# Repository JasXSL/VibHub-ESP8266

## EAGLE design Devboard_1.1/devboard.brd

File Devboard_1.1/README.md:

# Work in progress

Goal is to correct the errors in rev 1.0 and make additional improvements in the case additional devboard PCBs are made (likely given how cheap that is)

## TODO

~~Swap SDA/SCL pins on ESP8266 and header~~

~~Change I2C address to something not reserved (https://www.i2c-bus.org/addressing/)~~
Uses 0x60

~~Replace resistor array package to fit 0402 that the EXB28V actually uses (never trust what summary descriptions show)~~ Using EXB38V/0603x4 instead

~~Move buttons, obstructed by plugin boards~~

~~Add LED to driver enable/sleep, GPIO15~~

~~Add 0805 resistor (possibly 51R or 220R) to RGB LED 3v3 to limit overall brightness as needed~~

~~Add more spacing between GND pad and pins on DRV8833 package~~

~~Consider switching USB output ports V+ through 2.5mm jack switch to allow using only one port per channel at a time~~

~~Move jacks close to board edge~~

~~Add I2C header for great justice~~
Meh

~~Debug why auto flash and programming doesn't work~~
Reworked circuit, should work now

~~Remove auto boot mode since it may not even work and isn't required~~

~~Add instructions to slikscreen for manual flash boot mode~~
Not enough room to waste for this

~~Add FTDI style header near relocated flash and reboot pins (GND, CTS, VCC, TXD, RXD, RTS)~~

~~Add lables to FTDI header~~

~~Enlarged all text on silkscreen so its readable~~

~~Replace battery input with JST-XH (only needs silkscreen changes and more clearance)~~
Should be enough room now

~~Replace fuse to larger package with higher voltage rating~~

Other things

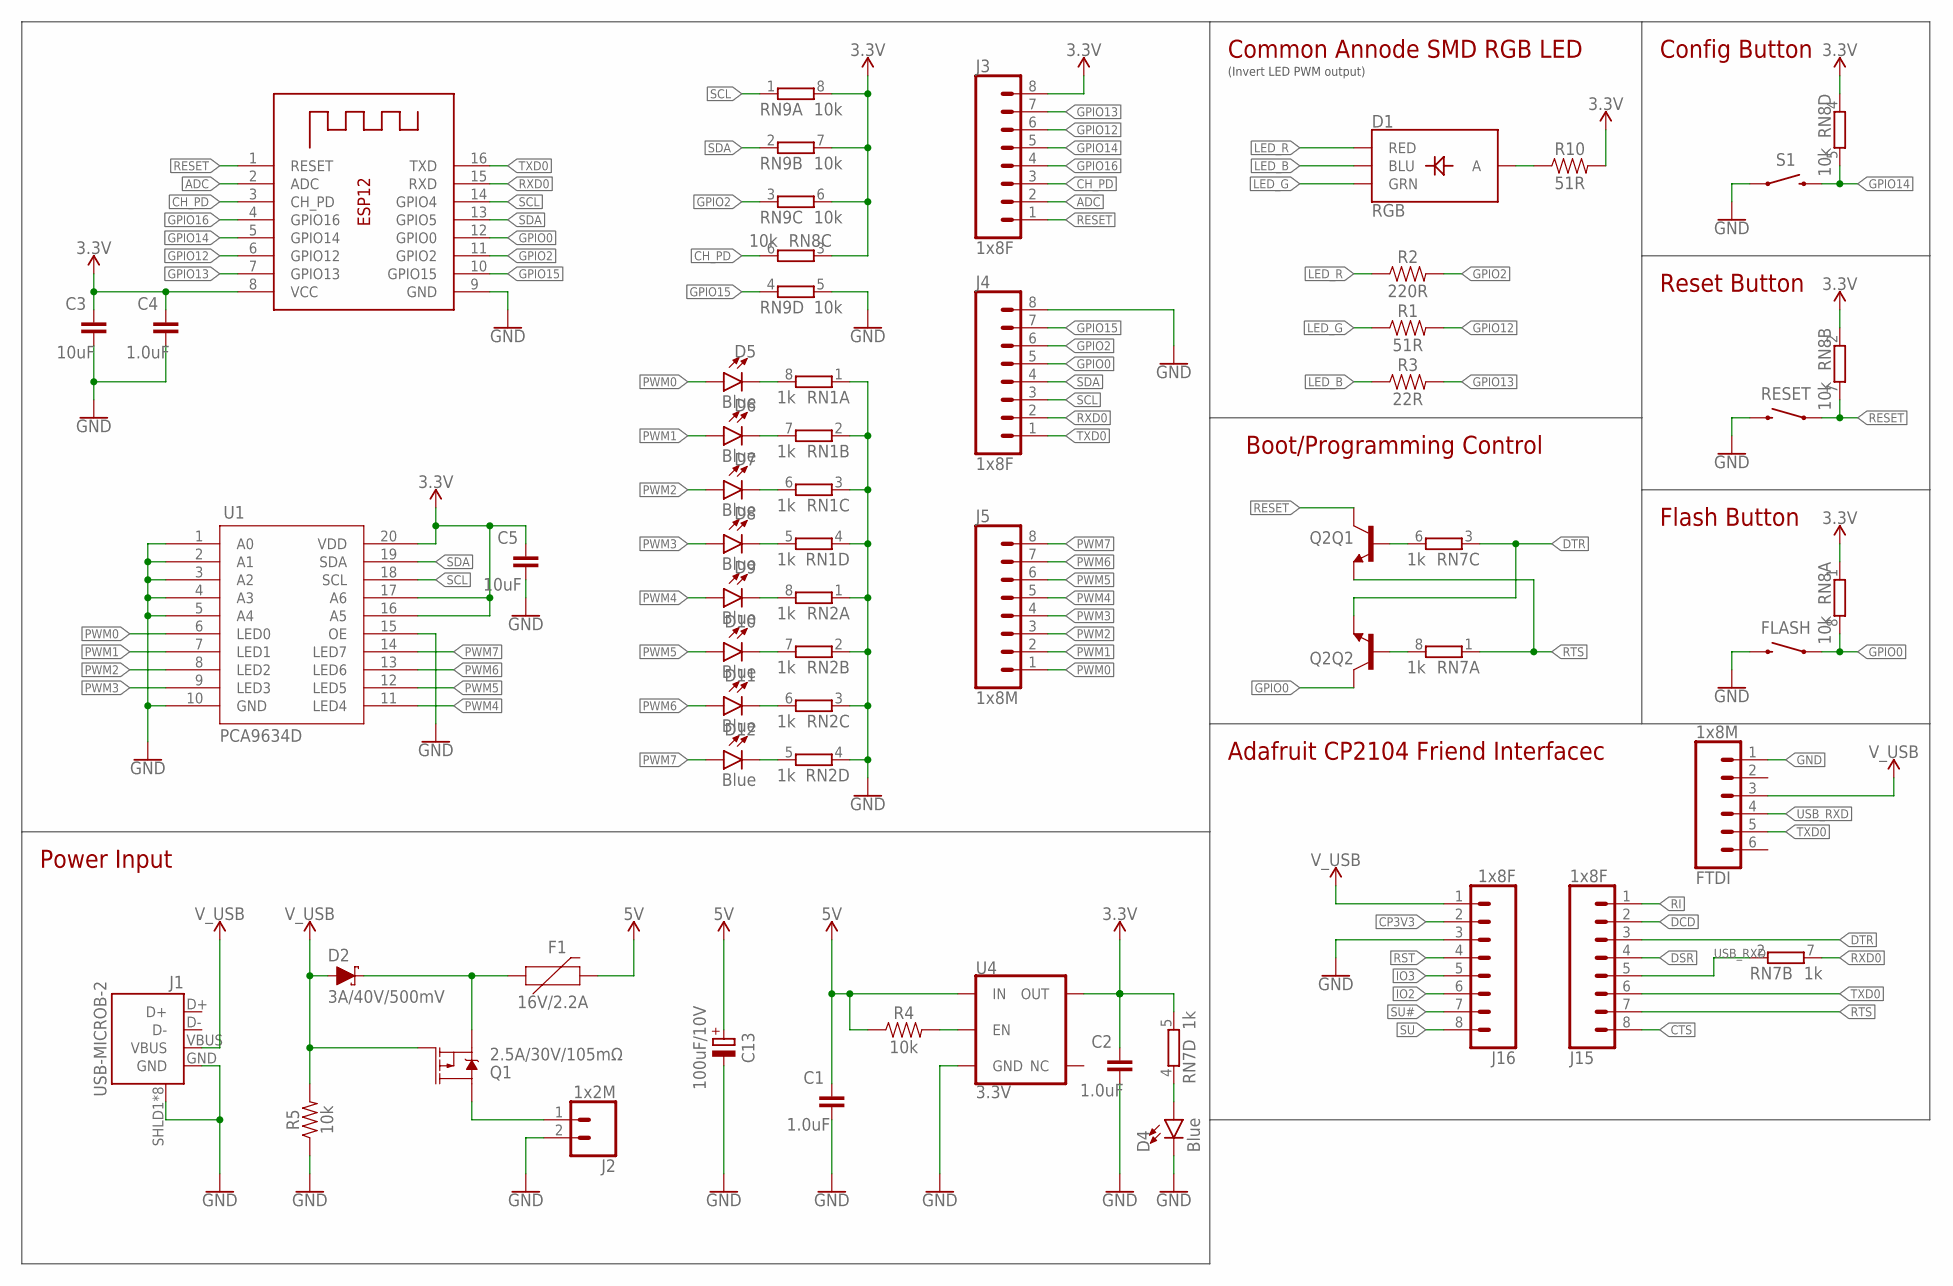
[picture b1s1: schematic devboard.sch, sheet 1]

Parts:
C1, C2, C4: 1.0uF; C0805
C3, C5: 10uF; C0805
C13: 100uF/10V; PANASONIC_D
D1: RGB; P-LCC-4-3
D2: 3A/40V/500mV; SMA-DIODE
D4, D5, D6, D7, D8, D9, D10, D11, D12: Blue; CHIPLED_0805_NOOUTLINE
F1: 16V/2.2A; FUSC7035X90
FLASH: MOMENTARY-SWITCH-SPST-SMD-6.0X3.5MM; TACTILE_SWITCH_SMD_6.0X3.5MM
FTDI: 1x8M; 1X06_LOCK
J1: USB-MICROB-2; USB-MICROB-10118194
J2: 1x2M; 1X02_LOCK_LONGPADS
J3, J4, J15, J16: 1x8F; 1X08_FEMALE_LOCK
J5: 1x8M; 1X08_LOCK
Q1: 2.5A/30V/105mΩ; SOT23-3
Q2: TRANS_NPN_DUAL-MBT3904DW1T1; SC70-6
R1, R10: 51R; 0805
R2: 220R; 0805
R3: 22R; 0805
R4, R5: 10k; 0805
RESET: MOMENTARY-SWITCH-SPST-SMD-6.0X3.5MM; TACTILE_SWITCH_SMD_6.0X3.5MM
RN1, RN2, RN7: 1k; EXB28V
RN8, RN9: 10k; EXB28V
S1: MOMENTARY-SWITCH-SPST-PTH-6.0MM; TACTILE_SWITCH_PTH_6.0MM
U1: PCA9634D; SOIC127P1032X265-20
U4: 3.3V; SOT23-5
X1: ESP12; ESP-12

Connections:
3.3V: C2.1, C3.1, C4.1, C5.1, J3.8, R10.2, RN7.5 (2), RN8.1, RN8.2 (1), RN8.3 (1), RN8.4 (1), RN9.6 (2), RN9.7 (2), RN9.8 (2), U1.16 (A5), U1.17 (A6), U1.20 (VDD), U4.5 (OUT), X1.8 (VCC); also elsewhere on the board
5V: C1.1, C13.+, F1.2, R4.1, U4.1 (IN); also elsewhere on the board
ADC: J3.2, X1.2 (ADC)
CH_PD: J3.3, RN8.6 (2), X1.3 (CH_PD)
CP3V3: J16.2
CTS: J15.8
DCD: J15.2
DSR: J15.4
DTR: J15.3, Q2.1 (E), RN7.3 (1)
GND: C1.2, C2.2, C3.2, C4.2, C5.2, C13.-, D4.C, FLASH.2, FTDI.1, J1.GND, J1.SHLD1 (SHIELD), J1.SHLD2 (SHIELD), J1.SHLD3 (SHIELD), J1.SHLD4 (SHIELD), J1.SHLD5 (SHIELD), J1.SHLD6 (SHIELD), J1.SHLD7 (SHIELD), J1.SHLD8 (SHIELD), J2.2, J4.8, J16.3, R5.1, RESET.2, RN1.1, RN1.2 (1), RN1.3 (1), RN1.4 (1), RN2.1, RN2.2 (1), RN2.3 (1), RN2.4 (1), RN9.5 (2), S1.1, U1.1 (A0), U1.2 (A1), U1.3 (A2), U1.4 (A3), U1.5 (A4), U1.10 (GND), U1.15 (OE), U4.2 (GND), X1.9 (GND); also elsewhere on the board
GPIO0: FLASH.1, J4.5, Q2.6 (C), RN8.8 (2), X1.12 (GPIO0)
GPIO2: J4.6, R2.2, RN9.3 (1), X1.11 (GPIO2)
GPIO12: J3.6, R1.2, X1.6 (GPIO12)
GPIO13: J3.7, R3.2, X1.7 (GPIO13)
GPIO14: J3.5, RN8.5 (2), S1.3 (2), X1.5 (GPIO14)
GPIO15: J4.7, RN9.4 (1), X1.10 (GPIO15); also elsewhere on the board
GPIO16: J3.4, X1.4 (GPIO16)
IO2: J16.6
IO3: J16.5
LED_B: D1.3 (BLU), R3.1
LED_G: D1.2 (GRN), R1.1
LED_R: D1.1 (RED), R2.1
unnamed: R4.2, U4.3 (EN)
unnamed: D5.C, RN1.8 (2)
unnamed: D6.C, RN1.7 (2)
unnamed: J2.1, Q1.3 (D)
unnamed: D2.C, F1.1, Q1.2 (S)
unnamed: D7.C, RN1.6 (2)
unnamed: D8.C, RN1.5 (2)
unnamed: D9.C, RN2.8 (2)
unnamed: D10.C, RN2.7 (2)
unnamed: D11.C, RN2.6 (2)
unnamed: D12.C, RN2.5 (2)
unnamed: D1.4 (A), R10.1
unnamed: Q2.2 (B), RN7.8 (2)
unnamed: Q2.5 (B), RN7.6 (2)
PWM0: D5.A, J5.1, U1.6 (LED0); also elsewhere on the board
PWM1: D6.A, J5.2, U1.7 (LED1); also elsewhere on the board
PWM2: D7.A, J5.3, U1.8 (LED2); also elsewhere on the board
PWM3: D8.A, J5.4, U1.9 (LED3); also elsewhere on the board
PWM4: D9.A, J5.5, U1.11 (LED4); also elsewhere on the board
PWM5: D10.A, J5.6, U1.12 (LED5); also elsewhere on the board
PWM6: D11.A, J5.7, U1.13 (LED6); also elsewhere on the board
PWM7: D12.A, J5.8, U1.14 (LED7); also elsewhere on the board
PWR_LED: D4.A, RN7.4 (1)
RESET: J3.1, Q2.3 (C), RESET.1, RN8.7 (2), X1.1 (RESET)
RI: J15.1
RST: J16.4
RTS: J15.7, Q2.4 (E), RN7.1
RXD0: J4.2, RN7.7 (2), X1.15 (RXD)
SCL: J4.3, RN9.1, U1.18 (SCL), X1.14 (GPIO4)
SDA: J4.4, RN9.2 (1), U1.19 (SDA), X1.13 (GPIO5)
SU: J16.8
SU#: J16.7
TXD0: FTDI.5, J4.1, J15.6, X1.16 (TXD)
USB_RXD: FTDI.4, J15.5, RN7.2 (1)
V_USB: D2.A, FTDI.3, J1.VBUS, J16.1, Q1.1 (G), R5.2

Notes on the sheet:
(Invert LED PWM output)
Reset Button
Config Button
Common Annode SMD RGB LED
Boot/Programming Control
Adafruit CP2104 Friend Interfacec
Power Input
Flash Button

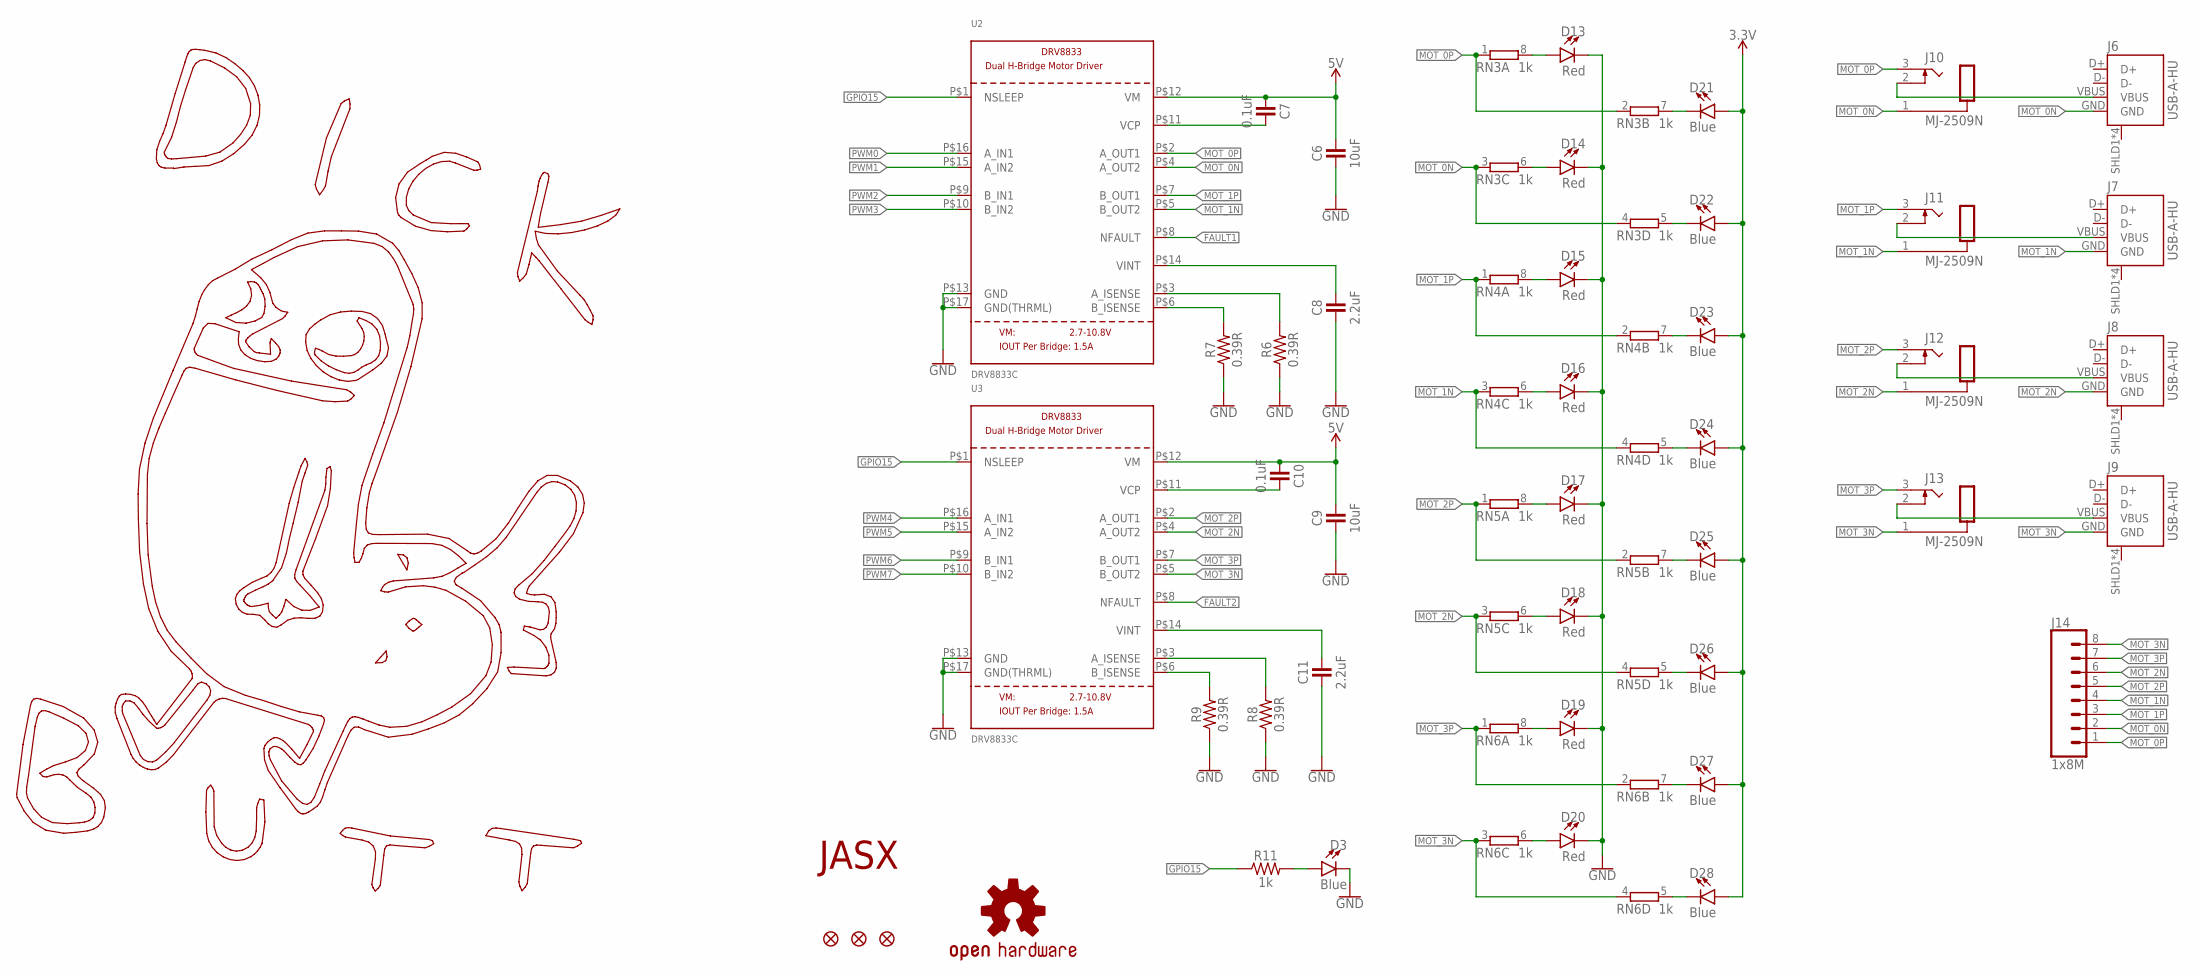
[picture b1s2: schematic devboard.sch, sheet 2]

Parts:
C6, C9: 10uF; C0805
C7, C10: 0.1uF; C0805
C8, C11: 2.2uF; C0805
D3, D21, D22, D23, D24, D25, D26, D27, D28: Blue; CHIPLED_0805_NOOUTLINE
D13, D14, D15, D16, D17, D18, D19, D20: Red; CHIPLED_0805_NOOUTLINE
FD1, FD2, FD3: FIDUCIAL1X2; FIDUCIAL-1X2
J6, J7, J8, J9: USB-A-HU
J10, J11, J12, J13: MJ-2509N
J14: 1x8M; 1X08_LOCK
LOGO1: OSHW-LOGOM; OSHW-LOGO-M
R6, R7, R8, R9: 0.39R; 0805
R11: 1k; 0805
RN3, RN4, RN5, RN6: 1k; EXB28V
U2, U3: DRV8833C; HTSSOP16
U$1: DICKBUTTCOPPER; DICKBUTT_COPPER
U$2: JASX_LOGO_LARGE; JASX_LOGO

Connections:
3.3V: D21.A, D22.A, D23.A, D24.A, D25.A, D26.A, D27.A, D28.A; also elsewhere on the board
5V: C6.2, C7.1, C9.2, C10.1, U2.P$12 (VM), U3.P$12 (VM); also elsewhere on the board
A_ISENSE0: R6.2, U2.P$3 (A_ISENSE)
A_ISENSE1: R8.2, U3.P$3 (A_ISENSE)
B_ISENSE0: R7.2, U2.P$6 (B_ISENSE)
B_ISENSE1: R9.2, U3.P$6 (B_ISENSE)
FAULT1: U2.P$8 (NFAULT)
FAULT2: U3.P$8 (NFAULT)
GND: C6.1, C8.1, C9.1, C11.1, D3.C, D13.C, D14.C, D15.C, D16.C, D17.C, D18.C, D19.C, D20.C, R6.1, R7.1, R8.1, R9.1, U2.P$13 (GND), U2.P$17 (GND(THRML)), U3.P$13 (GND), U3.P$17 (GND(THRML)); also elsewhere on the board
GPIO15: R11.1, U2.P$1 (NSLEEP), U3.P$1 (NSLEEP); also elsewhere on the board
MOT_0N: J6.GND, J10.1 (S), J14.2, RN3.3 (1), RN3.4 (1), U2.P$4 (A_OUT2)
MOT_0P: J10.3 (T), J14.1, RN3.1, RN3.2 (1), U2.P$2 (A_OUT1)
MOT_1N: J7.GND, J11.1 (S), J14.4, RN4.3 (1), RN4.4 (1), U2.P$5 (B_OUT2)
MOT_1P: J11.3 (T), J14.3, RN4.1, RN4.2 (1), U2.P$7 (B_OUT1)
MOT_2N: J8.GND, J12.1 (S), J14.6, RN5.3 (1), RN5.4 (1), U3.P$4 (A_OUT2)
MOT_2P: J12.3 (T), J14.5, RN5.1, RN5.2 (1), U3.P$2 (A_OUT1)
MOT_3N: J9.GND, J13.1 (S), J14.8, RN6.3 (1), RN6.4 (1), U3.P$5 (B_OUT2)
MOT_3P: J13.3 (T), J14.7, RN6.1, RN6.2 (1), U3.P$7 (B_OUT1)
unnamed: D3.A, R11.2
unnamed: J9.VBUS, J13.2 (TS)
unnamed: D21.C, RN3.7 (2)
unnamed: D13.A, RN3.8 (2)
unnamed: D14.A, RN3.6 (2)
unnamed: D15.A, RN4.8 (2)
unnamed: D16.A, RN4.6 (2)
unnamed: D17.A, RN5.8 (2)
unnamed: D18.A, RN5.6 (2)
unnamed: D19.A, RN6.8 (2)
unnamed: D20.A, RN6.6 (2)
unnamed: D22.C, RN3.5 (2)
unnamed: D23.C, RN4.7 (2)
unnamed: D24.C, RN4.5 (2)
unnamed: D28.C, RN6.5 (2)
unnamed: D27.C, RN6.7 (2)
unnamed: D26.C, RN5.5 (2)
unnamed: D25.C, RN5.7 (2)
unnamed: J6.VBUS, J10.2 (TS)
unnamed: J7.VBUS, J11.2 (TS)
unnamed: J8.VBUS, J12.2 (TS)
PWM0: U2.P$16 (A_IN1); also elsewhere on the board
PWM1: U2.P$15 (A_IN2); also elsewhere on the board
PWM2: U2.P$9 (B_IN1); also elsewhere on the board
PWM3: U2.P$10 (B_IN2); also elsewhere on the board
PWM4: U3.P$16 (A_IN1); also elsewhere on the board
PWM5: U3.P$15 (A_IN2); also elsewhere on the board
PWM6: U3.P$9 (B_IN1); also elsewhere on the board
PWM7: U3.P$10 (B_IN2); also elsewhere on the board
VCP0: C7.2, U2.P$11 (VCP)
VCP1: C10.2, U3.P$11 (VCP)
VINT0: C8.2, U2.P$14 (VINT)
VINT1: C11.2, U3.P$14 (VINT)

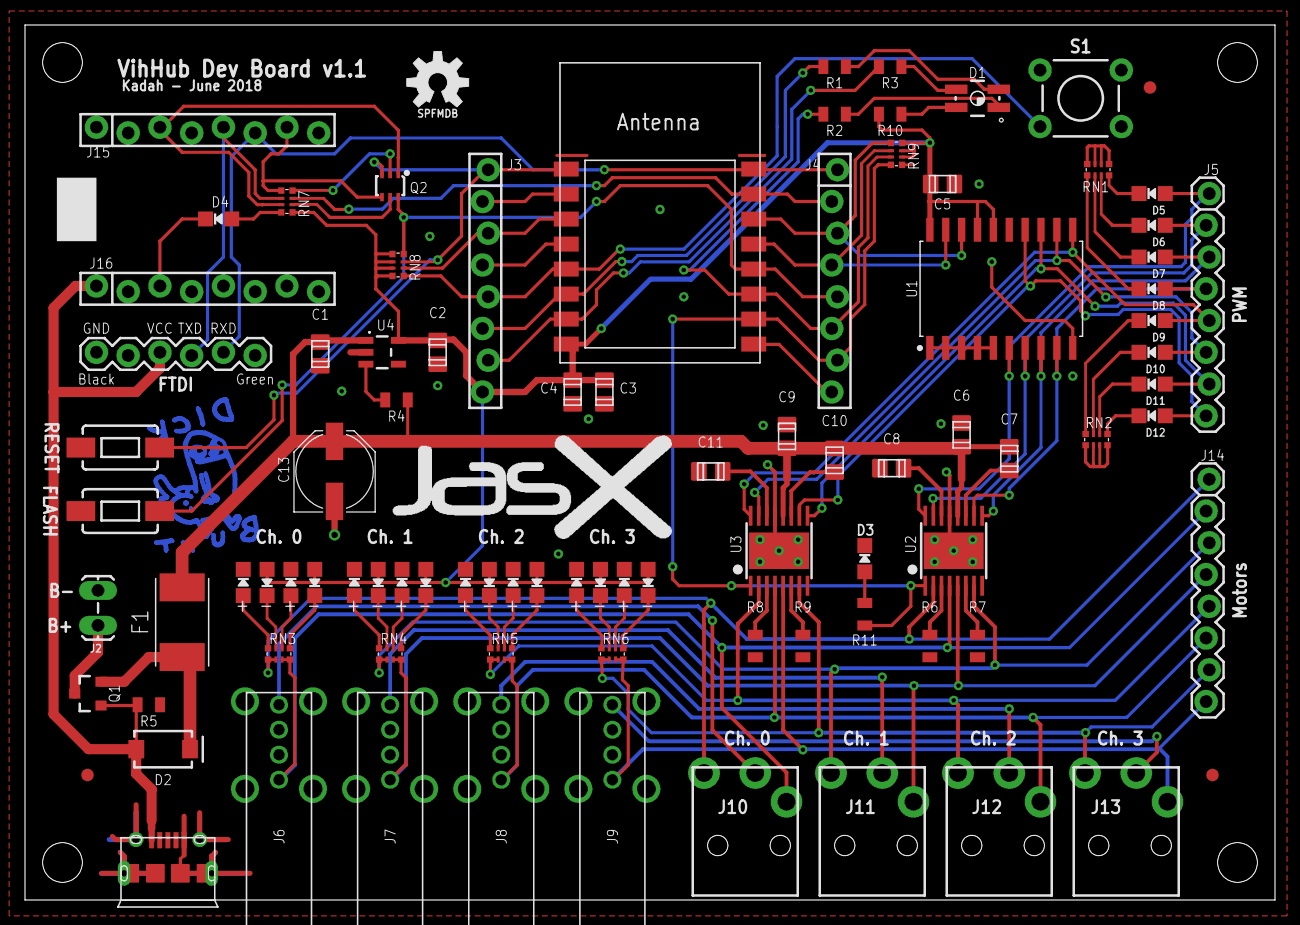
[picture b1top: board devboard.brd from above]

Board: 2 copper layers, 100.0 x 70.0 mm, 94 parts (1 on the bottom side), 84 nets.

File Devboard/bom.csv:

"Qty";"Value";"Device";"Package";"Parts";"Description";"DIGIKEY";"MF";"MPN";"OC_FARNELL";"OC_NEWARK";"PROD_ID";"SF_ID";"SF_SKU";"VALUE";
"2";"0.1uF/16V";"CAPACITOR-0805";"C0805";"C7, C10";"Capacitors";"";"";"";"";"";"";"";"";"";
"4";"0.43R";"RESISTOR0805";"0805";"R6, R7, R8, R9";"Generic Resistor Package";"";"";"";"";"";" ";"";"";" ";
"3";"1.0uF";"CAPACITOR-0805";"C0805";"C1, C2, C4";"Capacitors";"";"";"";"";"";"";"";"";"";
"1";"100uF/6.3V";"CAPACITOR-1206";"C1206";"C3";"Capacitors";"";"";"";"";"";"";"";"";"";
"2";"10k";"4R-NEXBS8V";"EXBS8V";"RN8, RN9";"Array Chip Resistor";"";"";"";"unknown";"unknown";"";"";"";"";
"2";"10k";"RESISTOR0805";"0805";"R4, R5";"Generic Resistor Package";"";"";"";"";"";" ";"";"";" ";
"1";"10uF";"CAPACITOR-0805";"C0805";"C5";"Capacitors";"";"";"";"";"";"";"";"";"";
"2";"10uF/16V";"CAPACITOR-1206";"C1206";"C6, C9";"Capacitors";"";"";"";"";"";"";"";"";"";
"1";"10uF/25V";"CAPACITOR_POLPANASONIC_D";"PANASONIC_D";"C12";"Polarized Capacitors";"";"";"";"";"";"";"";"";"";
"7";"1k";"4R-NEXBS8V";"EXBS8V";"RN1, RN2, RN3, RN4, RN5, RN6, RN7";"Array Chip Resistor";"";"";"";"unknown";"unknown";"";"";"";"";
"2";"1x2M";"CONN_02LOCK_LONGPADS";"1X02_LOCK_LONGPADS";"J2, J17";"Multi connection point. Often used as Generic Header-pin footprint for 0.1 inch spaced/style header connections";"";"";"";"";"";"";"";"";"";
"4";"1x8F";"CONN_08FEMALE_LOCK";"1X08_FEMALE_LOCK";"J3, J4, J15, J16";"Multi connection point. Often used as Generic Header-pin footprint for 0.1 inch spaced/style header connections";"";"";"";"";"";"CONN-09233";"PRT-09279";"";"";
"2";"1x8M";"CONN_08LOCK";"1X08_LOCK";"J5, J14";"Multi connection point. Often used as Generic Header-pin footprint for 0.1 inch spaced/style header connections";"";"";"";"";"";"";"";"";"";
"2";"2.2uF/16V";"CAPACITOR-1206";"C1206";"C8, C11";"Capacitors";"";"";"";"";"";"";"";"";"";
"1";"2.5A/30V/105mΩ";"MOSFET_PCH-DMG2307L";"SOT23-3";"Q1";"P-channel MOSFETs";"";"";"";"";"";"TRANS-11308";"";"";"2.5A/30V/105mΩ";
"1";"220R";"RESISTOR0805";"0805";"R2";"Generic Resistor Package";"";"";"";"";"";" ";"";"";" ";
"1";"22R";"RESISTOR0805";"0805";"R3";"Generic Resistor Package";"";"";"";"";"";" ";"";"";" ";
"1";"3.3V";"V_REG_AP2112K-3.3V";"SOT23-5";"U4";"AP2112 - 600mA CMOS LDO Regulator w/ Enable";"";"";"";"";"";"VREG-12457";"";"";"3.3V";
"1";"3A/40V/500mV";"DIODE-SCHOTTKY-B340A";"SMA-DIODE";"D2";"Schottky diode";"";"";"";"";"";"DIO-09886";"";"";"3A/40V/500mV";
"1";"51R";"RESISTOR0805";"0805";"R1";"Generic Resistor Package";"";"";"";"";"";" ";"";"";" ";
"1";"8V/2.2A";"PPTC_HALF-AMP";"1206";"F1";"Resettable Fuse PPTC";"";"";"";"";"";"RES-08585";"";"";"6V/0.5A";
"1";"BSS138PS";"BSS138PS";"SOT363";"T1";"Dual N-Channel MOSFET";"";"";"";"";"";"";"";"";"";
"17";"Blue";"LED0805-NO_OUTLINE";"CHIPLED_0805_NOOUTLINE";"D4, D5, D6, D7, D8, D9, D10, D11, D12, D21, D22, D23, D24, D25, D26, D27, D28";"LED (Generic)";"";"";"";"";"";"";"";"";"";
"2";"DRV8833C";"DRV8833";"HTSSOP16";"U2, U3";"DRV8833 Dual H-Bridge Motor Driver -- HTSSOP Package";"";"";"";"";"";"";"";"";"";
"1";"ESP12";"ESP-12";"ESP-12";"X1";"";"";"";"";"";"";"";"";"";"";
"3";"FIDUCIAL1X2";"FIDUCIAL1X2";"FIDUCIAL-1X2";"FD1, FD2, FD3";"Fiducial Alignment Points";"";"";"";"";"";"";"";"";"";
"4";"MJ-2509N";"MJ-2509N";"MJ-2509N";"J10, J11, J12, J13";"Mono Audio Jack, 2.5 MM";"";"";"";"";"";"";"";"";"";
"3";"MOMENTARY-SWITCH-SPST-PTH-6.0MM";"MOMENTARY-SWITCH-SPST-PTH-6.0MM";"TACTILE_SWITCH_PTH_6.0MM";"FLASH, RESET, S1";"Momentary Switch (Pushbutton) - SPST";"";"";"";"";"";" SWCH-08441";"";"COM-00097";"";
"1";"OSHW-LOGOM";"OSHW-LOGOM";"OSHW-LOGO-M";"LOGO1";"Open-Source Hardware (OSHW) Logo";"";"";"";"";"";"";"";"";"";
"1";"PCA9634PW";"PCA9634";"TSSOP20";"U1";"";"";"";"";"";"";"";"";"";"";
"1";"RGB";"LED-RGB-CAPLCC";"P-LCC-4-3";"D1";"LED-RGB Diffused Common Anode";"";"";"";"";"";"DIO-12986";"";"";"RGB";
"8";"Red";"LED0805-NO_OUTLINE";"CHIPLED_0805_NOOUTLINE";"D13, D14, D15, D16, D17, D18, D19, D20";"LED (Generic)";"";"";"";"";"";"";"";"";"";
"4";"USB-A-HU";"USB-A-HU";"USB-A-HU";"J6, J7, J8, J9";"USB Connectors";"";"";"";"";"";"";"";"";"";
"1";"USB-MICROB-2";"USB-MICROB-2";"USB-MICROB-10118194";"J1";"USB Connectors";"609-4618-6-ND ";"";"";"";"";"";"";"";"";

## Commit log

2018-01-17 First commit
    Shit's borked yo.
2018-01-17 Rename VibHub
    Naming conventions
2018-01-17 It twerks!
    You'll have to specify your wifi credentials, but you can now control PWM of a single pin via the websocket API.
2018-01-17 Add library
    Added modified version of library: washo4evr/Socket.io-v1.x-Library
2018-01-19 Add Config library with read/write to file, also connection library
    It doesn't work. But it compiles and doesn't crash. Around here we call that a win!
2018-01-20 Wtf
    BLE says it works, but it's not...
2018-01-20 Added captive portal demo
2018-01-22 Fixed host name passed to client
    Host name passed to client connection as missing last character due to len being off by one.
2018-01-22 Added config and connection to CaptivePortal Refactored config for JSON and added ESP8266 support Enabled debug on websockets Added flash format to reset function
2018-01-24 Compiles for ESP32 now but doesn't work due to current library flux
2018-01-29 Updated Captive Portal (Mostly nonfunctional)
2018-01-29 Added CaptivePortal2 which supports both ESP8266 and ESP32
2018-01-30 Updated pins for ESP32 devkit board
2018-01-30 Added support for Adafruit Motor Shield v2 (buggy)
2018-01-31 Jas ESP32 Attempt
    Took out the motor stuff for now. Next will be to improve the captive portal.
2018-01-31 PWM LED control
2018-01-31 Add back my old motor control
    This will work with my 4x motor controller chip that I have at hand. It's PWM, not rocket science :cat:
2018-01-31 Change the wifi-reset button to a winfi-config button
    When touched while the app is running, the wifi will enter config mode without resetting the data. Hitting the exit button on the front page now also closes the connection and restarts.
    Also adds a parameter to the wifi manager with device ID, however, this doesn't seem to work. I've created an issue request on the original library.
2018-02-01 Added captive portal config Added Config class and moved wifimanager to that Removed motor lib, was broken
2018-02-01 Updates to LED etc
    - Moved all filesystem config values into Config library.
    - Structured the code a bit for easier collapsing
    - Added program "states" which are signalled by the power of LEDs.
    - Moved the current motor implementation into VhPwm which is a generic class to easily setup and control GPIO PWM.
    - Added a motor class that extends VhPwm, but will later use to add additional functionality to motors (Programs).
    - Added reset detection by holding the button for 5 sec.
2018-02-02 Split Wifi, Socket.io, led, config in to their own classes Cleaned up the ino a lot Added invert to VhPmw Added Configuration.h for common settings Changed motor control class to global single Droppi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
2018-02-02 Added ESP32 pin map
2018-02-02 Add the rest of the config
    Server and port added
2018-02-02 Reset to factory on reboot
    Holding button while booting now resets to factory
2018-02-03 Added basic schematic
2018-02-03 Restructured VhSocket class as child of SocketIoClient for greater flexiblity
2018-02-03 Added button UI demo Updated Config
2018-02-03 It's bork :dog2:
    vhConf not defined in WiFiManager.cpp @ line 567
2018-02-03 Forgot wifi manager
    hurdur
2018-02-04 Good enough
    Finished stylizing the portal. Next SCIENCE will be programs.
2018-02-05 Large update and restructuring Button UI implemented Moved button handling to its own class Added SocketIoClass fork Fixed disconnect event Change SocketIO wrapper to Client Fixed SocketIO disconnect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
2018-02-05 Removed links to unneeded external libs
2018-02-05 Add program data
    Begun adding stuff for tweening programs
2018-02-05 Add programs
    Programs actually work, would you belive it? But easing was not implemented.
2018-02-06 Removed old code
2018-02-06 Modified how LED_INVERT works
2018-02-06 Added pulse effect to LED
2018-02-06 Add easing
    Adds easing and moves the tweening library into the root folder as I had to make a few changes to make it work and support all tween types.
2018-02-06 Increase max stages
    Changed max stages of timelines to 64. ESP32 should definitely have enough memory for that.
2018-02-06 Multiport!
    Received data for programs can now be a JSON array OR object of programs to run. Useful to run different programs on different ports.
2018-02-07 Added USB-to-UART interface
2018-02-09 Added Jas's motor code
2018-02-09 Added input protection Added motor drivers Added motor outputs Added 12V DC input (motors only) Untested, will likely catch fire
2018-02-09 Added TB6612FNG driver option to schematic
2018-02-12 Fleshed out the external power better This more likely will work now
2018-02-12 Remove legacy stuff
2018-02-19 Added ESP8266
2018-02-19 Add motor update
    Feel free to revise to make it prettier and better. This makes programs work at least :3
2018-02-19 Change port syntax
    Port is now a bitwise combination so you can send a single program to multiple specific ports.
2018-02-19 Added ESP8266 support to main code
2018-04-27 Adds in programs once more
2018-04-28 Added initial ESP8266 i2c version (wip)
2018-05-02 Add old wifi manager
2018-05-02 Clean up old stuff, see the legacy branch for that
2018-05-02 remove ESP32
2018-05-04 Added sketch for testing PCA9634 function
    Does sin wave across the 8 channels
    Blinks GPIO15
    Scans I2C bus for active addresses on boot
2018-05-11 Added DRV8833 test sketch
2018-05-19 Finished DRV8833 intergration
2018-05-22 Added devboard PCB
2018-05-22 Added vibhub eagle lib
    Actual design files use library.io managed one that cannot be shared still due to library.io still not supporting that 5 months after launch...
2018-05-22 Added gerber.cam
2018-05-24 Revised dev board PCB layout Added rough draft BOM
2018-05-24 Formated BOM
2018-05-25 Updated dev board, replaced some parts that are not generally available
2018-05-25 Fixed silkscreen
2018-05-25 Updated BOM
2018-05-25 Increased motor driver current
2018-05-27 Final changes to dev board for manufacture
2018-05-29 Updated BOM Renamed 1.0 gerber zip Removed unneeded temp file
2018-05-29 Changed fuse rating
2018-05-29 Add schematics
    Adds some schematics
2018-05-29 - Added DEBUG_DUTY preprocessor definition to PCA9634.cpp to prevent massive spam in programs - P events now turn off programs - Fixed some program debuggery - Programs will no longer update PWM afte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
2018-06-03 Archived devboard 1.0
2018-06-03 Fixed devboard 1.0 BOM, again
2018-06-03 Added readme warning about 1.0 board error
2018-06-03 Started devboard 1.1
2018-06-07 Revert "Merge branch 'master' of https://github.com/JasXSL/VibHub-ESP32"
    This reverts commit e7525410c98c27a43733a001509c30d6c5395b8a, reversing
    changes made to 8ce02802e0bd9013257f2d88e97262cd868c22ea.
2018-06-07 Randobject implementation
2018-06-09 enable debug
2018-06-09 rescript because ArduinoJson fail
2018-06-09 tween fixing
2018-06-09 Updates to 1.1 board
2018-06-09 TweenDuino Debugger
2018-06-09 Revert "Merge branch 'master' of https://github.com/JasXSL/VibHub-ESP32"
    This reverts commit e7525410c98c27a43733a001509c30d6c5395b8a, reversing
    changes made to 8ce02802e0bd9013257f2d88e97262cd868c22ea. (reverted from commit 0353e5c721b89ea74c99468aca303392ed431fdb)
2018-06-10 Hopefully fixed PCA9634 not responding after ESP reset
2018-06-11 Updated PCA9634 test
2018-06-11 Improved PCA9634 reset
2018-06-11 Fixed initial motor state on (re)start
2018-06-17 Added reset support to TweenDuino
2018-06-17 Improved memory leak to be slightly less leaky Added memory use debug message
2018-06-17 Fixed memory leak with programs (hopefully)
2018-06-18 Fixed memory leak with TweeenDuino
2018-06-18 Add some debug definitions. Make short & randobj programs work.
2018-06-18 Revert "Revert "Merge branch 'master' of https://github.com/JasXSL/VibHub-ESP32""
    This reverts commit d77c9c4687c02bab05891224d50b813a23a65ead.
2018-06-18 Revert "Revert "Merge branch 'master' of https://github.com/JasXSL/VibHub-ESP32""
    This reverts commit 0353e5c721b89ea74c99468aca303392ed431fdb.
2018-06-18 Prepare!
2018-06-18 Index page done
2018-06-18 more CSS wizardry
2018-06-19 Updated devboard 1.1
2018-06-19 All of the wifi portal
2018-06-20 Add manual
    Here's a libreoffice based manual.
2018-06-21 Added draft flashing instructions
2018-06-21 Updated 1.1 board
2018-06-23 More updates to PCA9634 lib
2018-06-24 1.1 board finalizations
2018-06-25 1.1 dev board RTM
2018-06-25 QR Code
2018-06-26 WiFiManager is still really buggy, but at least it looks good whenever it actually works
2018-07-05 Updated PCA9634 lib for 1.1 dev board
2018-07-05 output memory info and remove some quote marks
2018-07-16 Added board test sketch, initial version Currently only has basic test patterns to help verify assembly
2018-07-20 Updated board test
2018-08-07 DeviceID is now 12 bytes, uppercase, and has numbers. Removed unused generateDeviceID method Made deviceID use a monospace font
2018-08-11 Remove custom WiFiManager
    Latest official release seems to work well
2018-08-21 - Fix for randObjects max nr being off by 1 - Fix for motor maxing out after completing the first program upon reset
2018-08-22 Increase tween timeline max size. It should now support some 40 or so stages
2018-08-29 Backports tweening from ESP32
2018-08-30 New CSS but doesn't work due to esp8266 memory constraints
2018-08-30 Removes the custom CSS and adds device ID to the config page. Should work with the low memory ESP8266
2019-08-08 Update JSON
2019-08-08 Remove some esp32 stuff
